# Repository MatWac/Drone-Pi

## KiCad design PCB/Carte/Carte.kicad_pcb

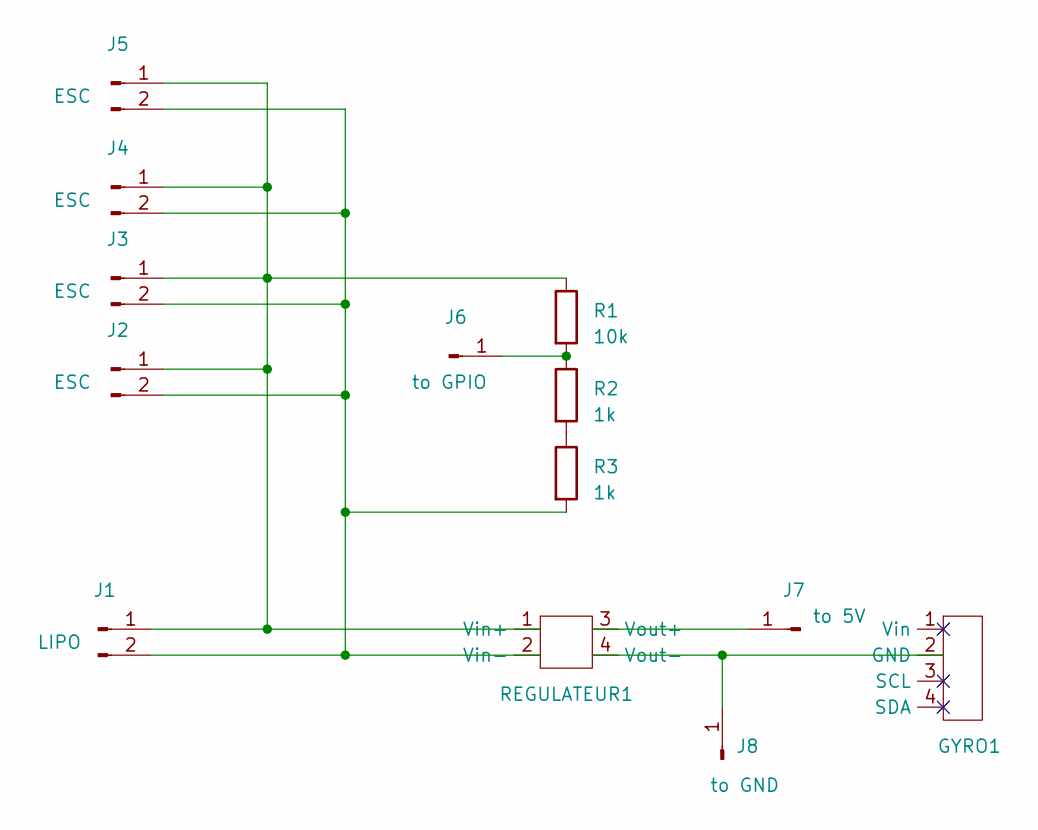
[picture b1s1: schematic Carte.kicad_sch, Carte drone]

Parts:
GYRO1: MPU-6050
J1: LIPO; 2Pin
J2, J3, J4, J5: ESC; 2Pin
J6: to GPIO; 1Pin
J7: to 5V; 1Pin
J8: to GND; 1Pin
R1: 10k; R
R2, R3: 1k; R
REGULATEUR1: LM2596S

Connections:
unnamed: GYRO1.2 (GND), J8.1, REGULATEUR1.4 (Vout-)
unnamed: J1.1, J2.1, J3.1, J4.1, J5.1, R1.1, REGULATEUR1.1 (Vin+)
unnamed: J1.2, J2.2, J3.2, J4.2, J5.2, R3.2, REGULATEUR1.2 (Vin-)
unnamed: J6.1, R1.2, R2.1
unnamed: J7.1, REGULATEUR1.3 (Vout+)
unnamed: R2.2, R3.1

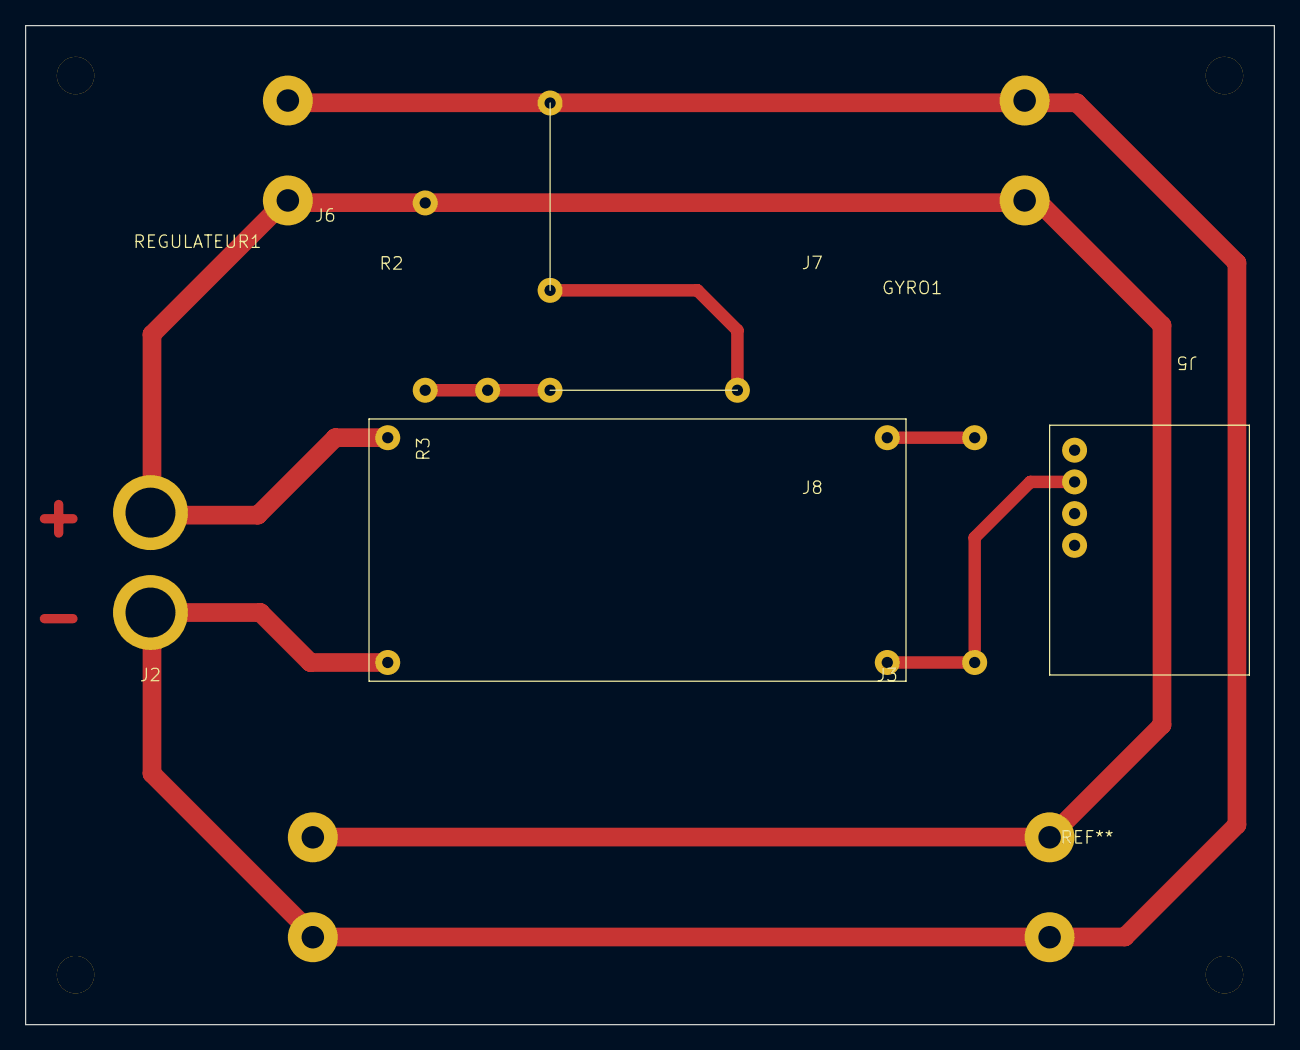
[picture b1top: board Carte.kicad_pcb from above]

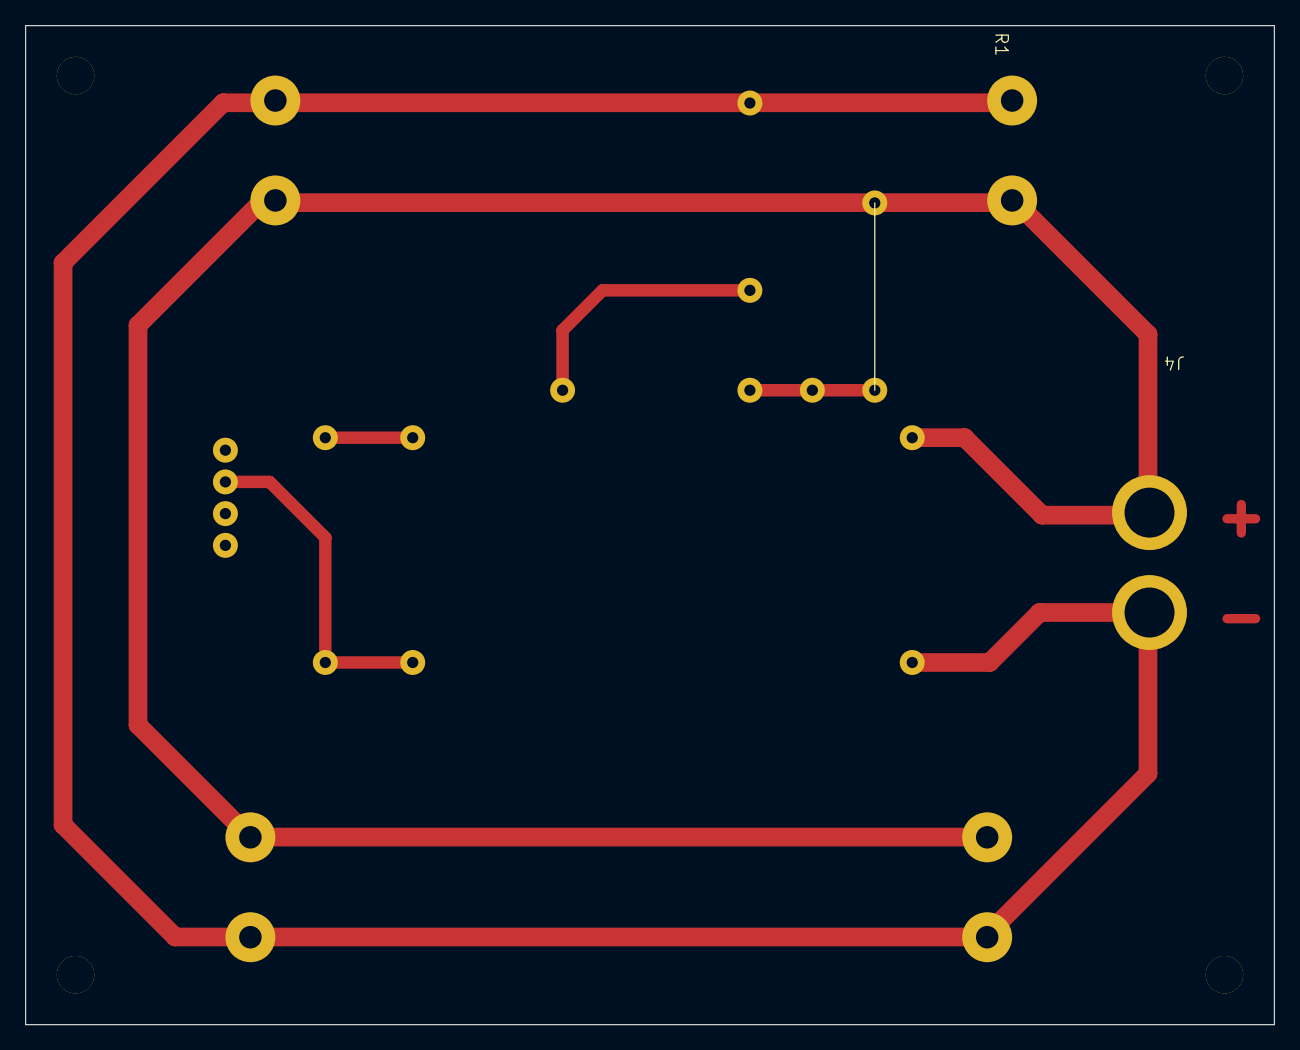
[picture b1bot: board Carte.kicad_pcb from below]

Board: 2 copper layers, 100.0 x 80.0 mm, 13 parts (2 on the bottom side), 6 nets.

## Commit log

2023-03-02 PCB + CAO
2023-03-06 Frame
2023-05-17 DRONE_PI
2024-03-18 New Frame
2024-04-13 Code
2024-04-13 New Frame + Ekf
2024-10-09 Remove ekf
